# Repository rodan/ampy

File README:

an audio amplifier project that contains a mixer controlled by an MSP430 microcontroller

contents:
 hardware/power_amp  - power circuit for the amplifier
 hardware/power_pre  - power circuit used by the mixer board
 hardware/amp        - 2x25W amplifier. for a quad setup this board is used twice, for 6 channels it's used 3 times.
 hardware/mixer      - mixer board. 10 inputs, 6 outputs, 12 channels of mixing. a stereo-to-quad panning circuit is included

 firmware_mixer      - software that runs on the MSP430F5510 that is present on the mixer board
 firmware_brain      - software for the main uC (CC430F5137) that interfaces the user with the mixer board. currently user input comes via remote control presses.
 firmware_display    - software that runs on the atmega present on the BADGEr. this is a simple adaptation on Jeremy Blum's "Pi BADGEr ePaper Weather Station".

 linux               - linux client that talks over a serial link to firmware_brain and controls the mixer and the power amp

pictures now available: https://photos.app.goo.gl/L8txqSKrcZFV2BbR8

--------------------------------------------

Mixer board input

two different input methods are available, either via UART or I2C. since they use the exact same 2 pins the switch between them is a compile time option - see config.h. the i2c interface is highly recommended.

I2C implementation

the communication protocol consists of either a direct 14 byte read in which case the current settings are being shared, 2 byte writes for sending commands or 4 byte writes for sending new volume values. the slave address is 0x28.

UART commands
v___   set volume
 ||+ volume - [0-255]
 |+- channel - {r,l,b}
 +-- pga ID - [1-6]
     1: front, 2: rear, 3: line-in
     4: spdif, 5: front-rear pan, 6: center and subwoofer
m_     mute pga
 +- pga ID - [1-6]
u_     unmute pga
 +- pga ID - [1-6]
w_     write current settings to flash
 +- location [1-3]
r_     load saved settings from flash
 +- location [1-3]
s      show settings
?      show help

 homepage:        https://github.com/rodan/ampy
 author:          Petre Rodan <2b4eda@subdimension.ro>
 license:         GNU GPLv3

 parts of the code were originally forked from the openchronos-ng project [1]. 
 linux mixer control code based on alsamixer [2]

 software requirements:

   msp430 toolchain

[1] http://openchronos-ng.sourceforge.net
[2] http://www.alsa-project.org

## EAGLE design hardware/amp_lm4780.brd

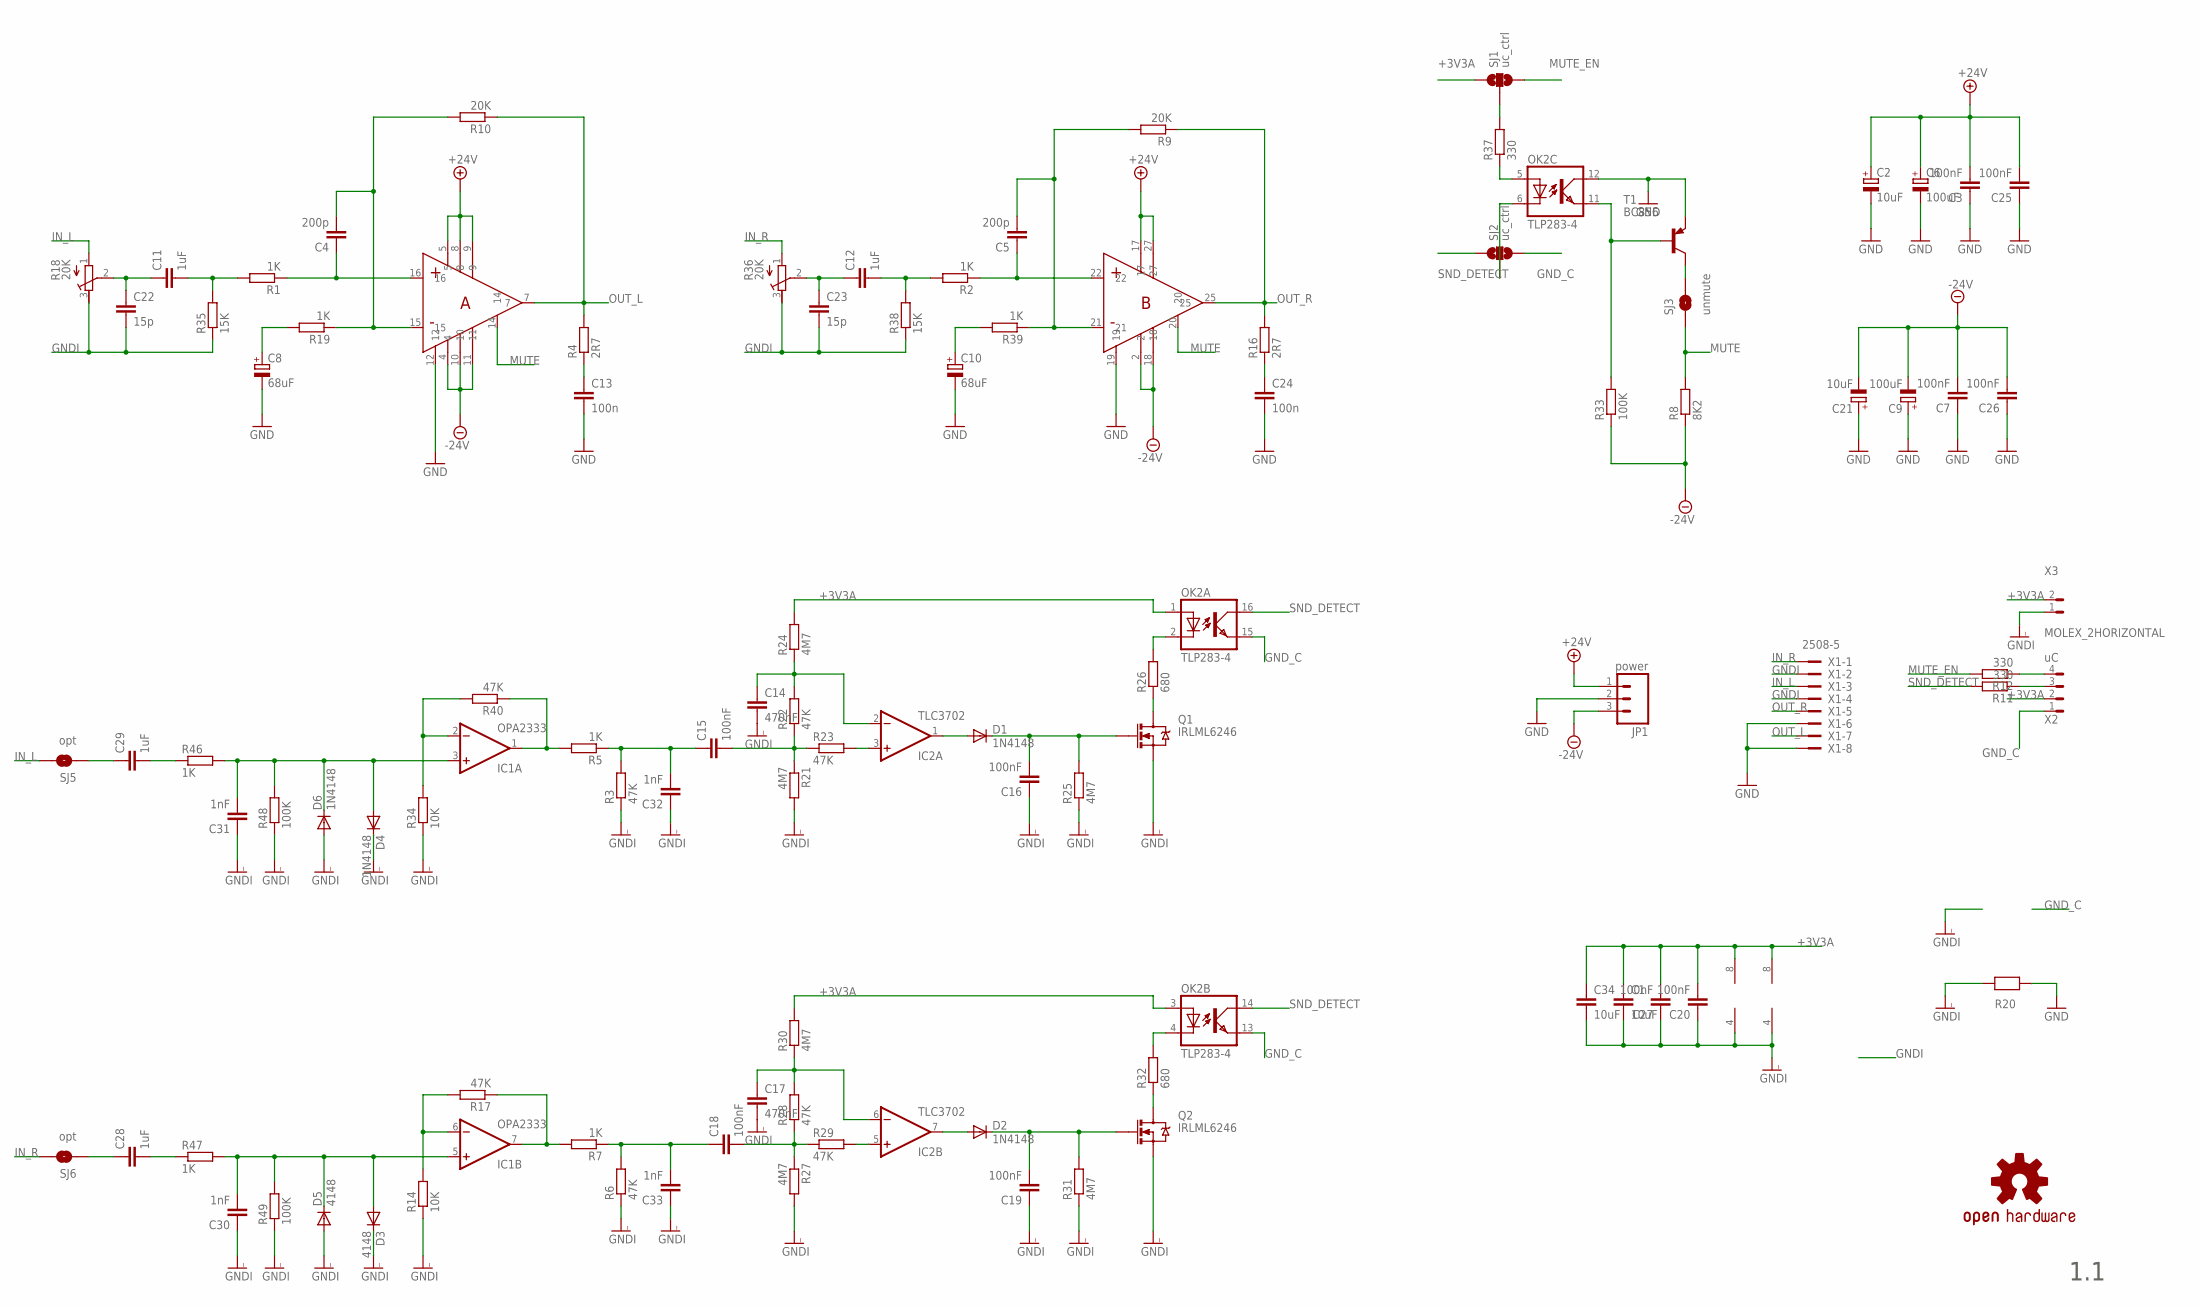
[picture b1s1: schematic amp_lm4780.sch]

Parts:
C1, C34: 10uF; C1206K
C2, C21: 10uF; PANASONIC_C
C3, C7, C15, C16, C18, C19, C20, C25, C26, C27: 100nF; C0805
C4, C5: 200p; C0805
C6, C9: 100uF; PANASONIC_G
C8, C10: 68uF; PANASONIC_E
C11, C12: 1uF; C050-035X075
C13, C24: 100n; C10B5
C14, C17: 470nF; C0805
C22, C23: 15p; C0805
C28, C29: 1uF; C0805
C30, C31, C32, C33: 1nF; C0805
D1, D2, D4, D6: 1N4148; SOD-123_MINI-SMA
D3, D5: 4148; SOD-123_MINI-SMA
IC1: OPA2333; SO08
IC2: TLC3702; SO08
JP1: power; 1X03
OK2: TLP283-4; MINI-FLAT-16
Q1, Q2: IRLML6246; SOT23-3
R1, R2, R5, R7, R46, R47: 1K; R0805W
R3, R6, R17, R22, R23, R28, R29, R40: 47K; R0805W
R4, R16: 2R7; P0613/15
R8: 8K2; R0805W
R9, R10: 20K; R0805W
R11, R12, R37: 330; R0805W
R14, R34: 10K; R0805W
R18, R36: 20K; RTRIM3339P
R19, R39: 1K; P0613/15
R20: 0R_0805; R0805W
R21, R24, R25, R27, R30, R31: 4M7; R0805W
R26, R32: 680; R0805W
R33, R48, R49: 100K; R0805W
R35, R38: 15K; R0805W
SJ1, SJ2: uc_ctrl; SJ_3_PASTE2&3
SJ3: unmute; SJ_2S-TRACE
SJ5, SJ6: opt; SJ_2S-TRACE
T1: BC856; SOT23-BEC
U$1: LM4780_H; TO220-27_HOR
U$7: OSHW-LOGOM; OSHW-LOGO-M
X1: 2508-5; PAK100/2500-5-08
X2: uC; 0530480401
X3: MOLEX_2HORIZONTAL; 0530480210

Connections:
+3V3A: C1.1, C20.2, C27.2, C34.1, IC1.8 (V+), IC2.8 (V+), OK2.1 (A), OK2.3 (A), R24.2, R30.2, SJ1.1, X2.2 (3), X3.2 (1)
+24V: C2.+, C3.2, C6.+, C25.2, JP1.1, U$1.5, U$1.8, U$1.9, U$1.17, U$1.27
-24V: C7.2, C9.-, C21.-, C26.2, JP1.3, R8.1, R33.1, U$1.2, U$1.4, U$1.10, U$1.11, U$1.18
GND: C2.-, C3.1, C6.-, C7.1, C8.-, C9.+, C10.-, C13.2, C21.+, C24.2, C25.1, C26.1, JP1.2, OK2.12 (COL), R20.2, T1.E, U$1.12, U$1.19, X1.6, X1.8
GNDI: C1.2, C14.2, C16.1, C17.2, C19.1, C20.1, C22.2, C23.2, C27.1, C30.1, C31.1, C32.1, C33.1, C34.2, D3.C, D4.C, D5.A, D6.A, IC1.4 (V-), IC2.4 (V-), Q1.2 (S), Q2.2 (S), R3.1, R6.1, R14.1, R18.3 (E), R20.1, R21.2, R25.1, R27.2, R31.1, R34.1, R35.1, R36.3 (E), R38.1, R48.1, R49.1, X1.2, X1.4, X3.1 (2)
GND_C: OK2.13 (EMIT), OK2.15 (EMIT), SJ2.3, X2.1 (4)
IN_L: R18.1 (A), SJ5.2, X1.3
IN_R: R36.1 (A), SJ6.2, X1.1
MUTE: R8.2, SJ3.1, U$1.14, U$1.20
MUTE_EN: R12.2, SJ1.3
unnamed: C5.2, R9.2, R39.1, U$1.21
unnamed: SJ3.2, T1.C
unnamed: R11.1, X2.3 (2)
unnamed: R12.1, X2.4 (1)
unnamed: IC1.6 (-IN), R14.2, R17.2
unnamed: C13.1, R4.1
unnamed: IC1.7 (OUT), R7.2, R17.1
unnamed: C4.1, R1.1, U$1.16
unnamed: C11.2, R1.2, R35.2
unnamed: C11.1, C22.1, R18.2 (S)
unnamed: C15.2, R21.1, R22.1, R23.1
unnamed: IC1.2 (-IN), R34.2, R40.2
unnamed: IC1.1 (OUT), R5.2, R40.1
unnamed: C24.1, R16.1
unnamed: D1.A, IC2.1 (OUT)
unnamed: C28.1, SJ6.1
unnamed: C30.2, D3.A, D5.C, IC1.5 (+IN), R47.2, R49.2
unnamed: C28.2, R47.1
unnamed: C29.1, SJ5.1
unnamed: IC2.3 (+IN), R23.2
unnamed: OK2.6 (C), SJ2.2
unnamed: Q1.3 (D), R26.1
unnamed: C14.1, IC2.2 (-IN), R22.2, R24.1
unnamed: C29.2, R46.1
unnamed: OK2.2 (C), R26.2
unnamed: C15.1, C32.2, R3.2, R5.1
unnamed: C31.2, D4.A, D6.C, IC1.3 (+IN), R46.2, R48.2
unnamed: C16.2, D1.C, Q1.1 (G), R25.2
unnamed: D2.A, IC2.7 (OUT)
unnamed: R37.2, SJ1.2
unnamed: C17.1, IC2.6 (-IN), R28.2, R30.1
unnamed: C18.2, R27.1, R28.1, R29.1
unnamed: C18.1, C33.2, R6.2, R7.1
unnamed: IC2.5 (+IN), R29.2
unnamed: C19.2, D2.C, Q2.1 (G), R31.2
unnamed: Q2.3 (D), R32.1
unnamed: OK2.4 (C), R32.2
unnamed: OK2.11 (EMIT), R33.2, T1.B
unnamed: C5.1, R2.1, U$1.22
unnamed: OK2.5 (A), R37.1
unnamed: C12.2, R2.2, R38.2
unnamed: C12.1, C23.1, R36.2 (S)
unnamed: C4.2, R10.2, R19.1, U$1.15
unnamed: C8.+, R19.2
unnamed: C10.+, R39.2
OUT_L: R4.2, R10.1, U$1.7, X1.7
OUT_R: R9.1, R16.2, U$1.25, X1.5
SND_DETECT: OK2.14 (COL), OK2.16 (COL), R11.2, SJ2.1

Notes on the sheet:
1.1

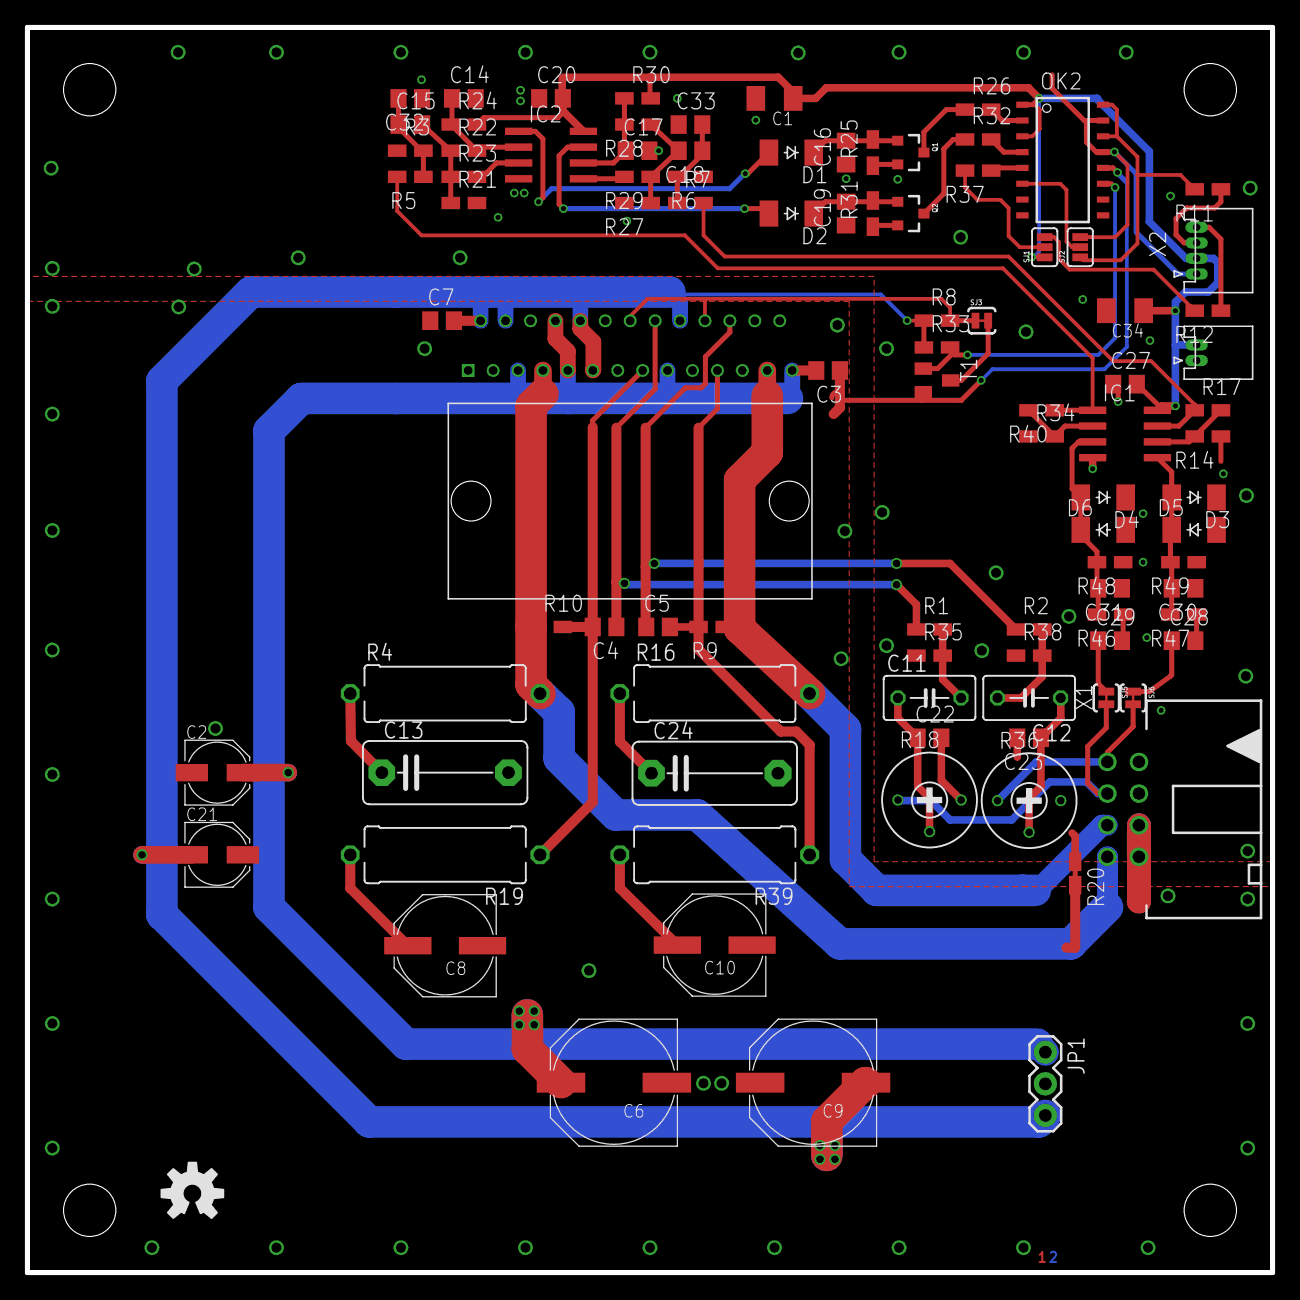
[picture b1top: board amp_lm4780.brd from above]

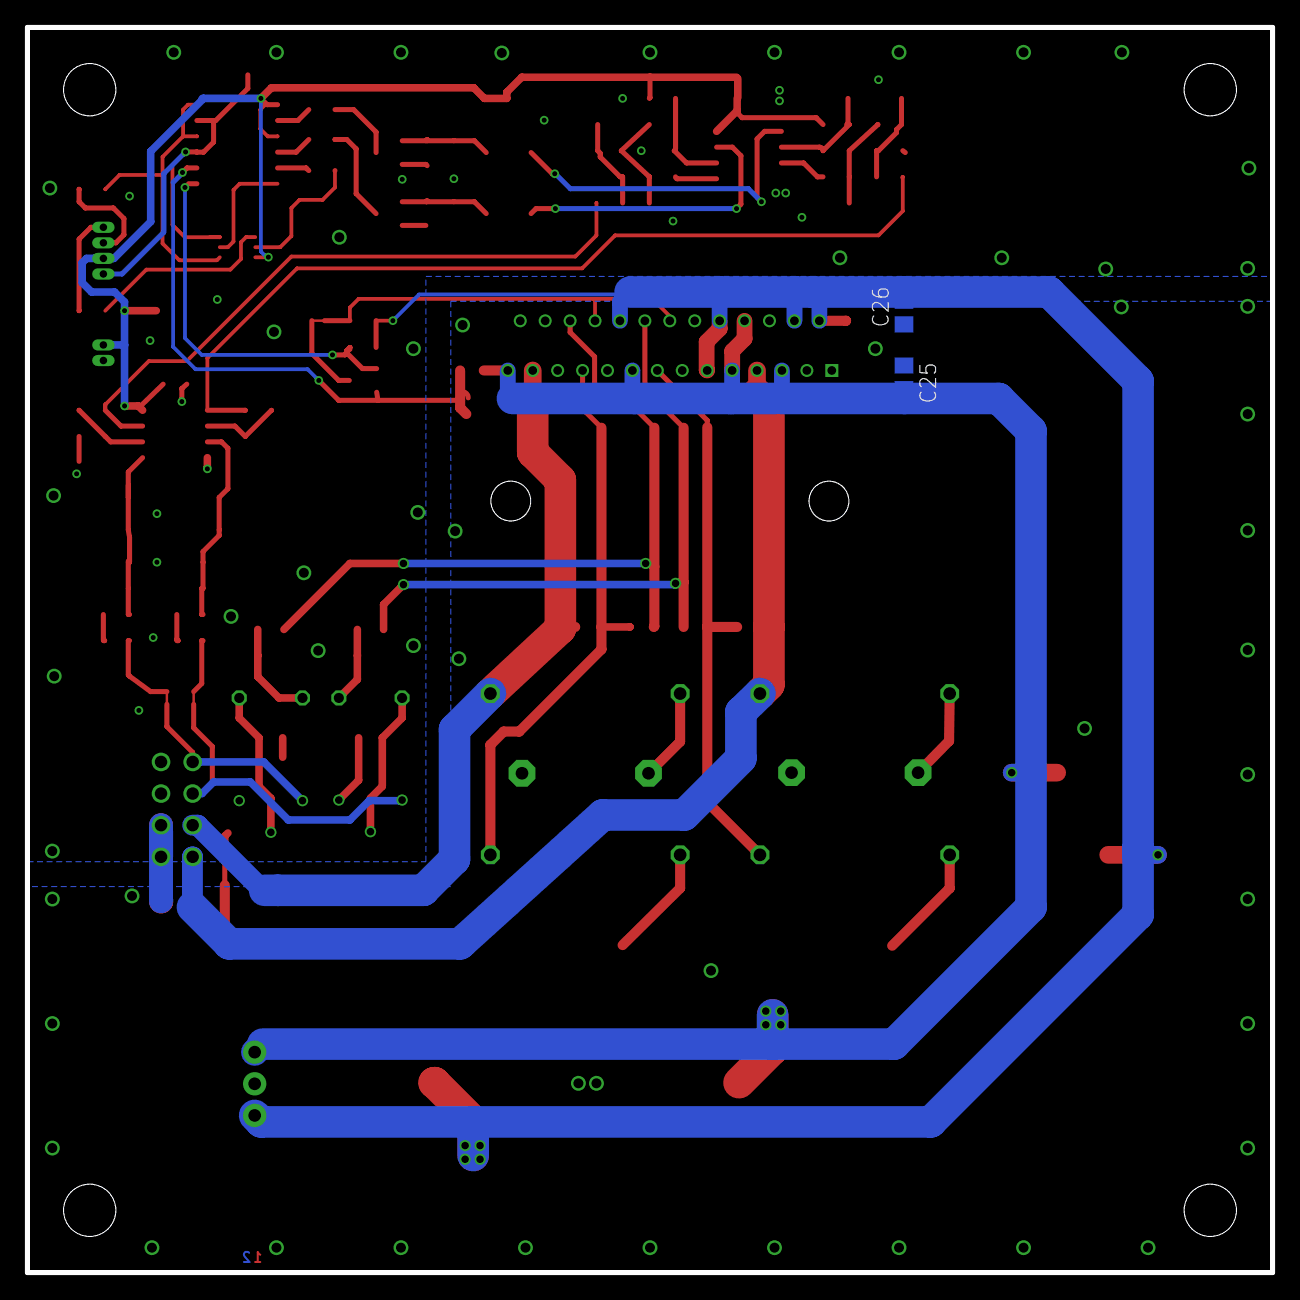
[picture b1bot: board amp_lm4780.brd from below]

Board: 4 copper layers, 100.0 x 100.0 mm, 99 parts (2 on the bottom side), 58 nets.

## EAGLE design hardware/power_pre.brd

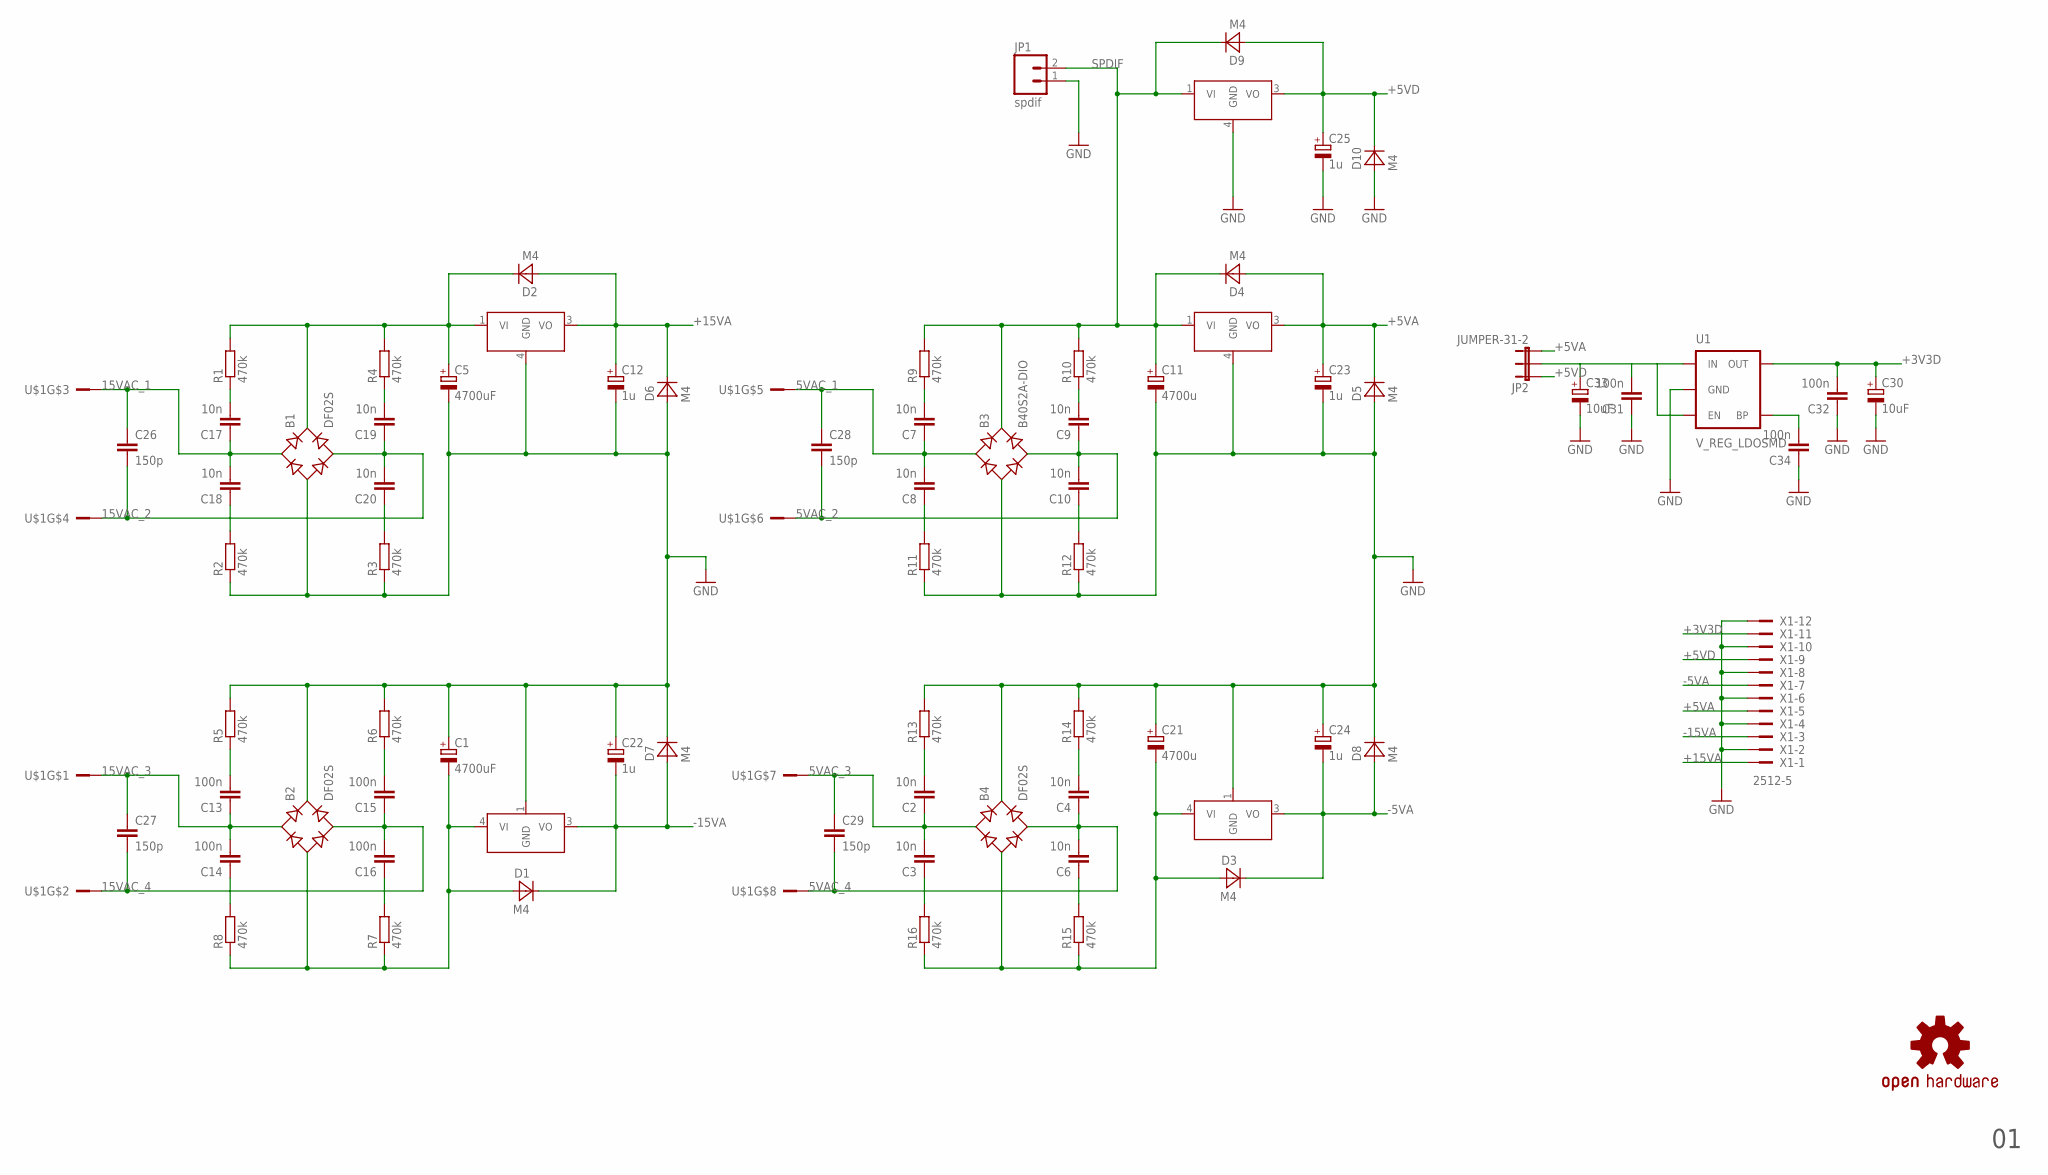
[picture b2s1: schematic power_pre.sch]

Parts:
B1, B2, B4: DF02S; DFS
B3: B40S2A-DIO; DFS
C1, C5: 4700uF; E7,5-18
C2, C3, C4, C6, C7, C8, C9, C10, C17, C18, C19, C20: 10n; C0805
C11, C21: 4700u; E7,5-16
C12, C22, C23, C24, C25: 1u; PANASONIC_B
C13, C14, C15, C16, C31, C32, C34: 100n; C0805
C26, C27, C28, C29: 150p; C5B4.5
C30, C33: 10uF; 153CLV-0405
D1, D2, D3, D4, D5, D6, D7, D8, D9, D10: M4; SMA
IC1: 7815; D2PACK
IC2: 7915; D2PACK
IC3, IC5: 7805; D2PACK
IC4: 7905; D2PACK
JP1: spdif; 1X02
JP2: JUMPER-31-2; SJ_3_PASTE1&2
R1, R2, R3, R4, R5, R6, R7, R8, R9, R10, R11, R12, R13, R14, R15, R16: 470k; R0805W
U1: V_REG_LDOSMD; SOT23-5
U$1: DEGSON_8
U$7: OSHW-LOGOM; OSHW-LOGO-M
X1: 2512-5; PAK100/2500-5-12

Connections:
5VAC_1: B3.AC1, C7.1, C8.2, C28.1, U$1.5
5VAC_2: B3.AC2, C9.1, C10.2, C28.2, U$1.6
5VAC_3: B4.AC1, C2.1, C3.2, C29.1, U$1.7
5VAC_4: B4.AC2, C4.1, C6.2, C29.2, U$1.8
15VAC_1: B1.AC1, C17.1, C18.2, C26.1, U$1.3
15VAC_2: B1.AC2, C19.1, C20.2, C26.2, U$1.4
15VAC_3: B2.AC1, C13.1, C14.2, C27.1, U$1.1
15VAC_4: B2.AC2, C15.1, C16.2, C27.2, U$1.2
+3V3D: C30.+, C32.2, U1.5 (OUT), X1.11
+5VA: C23.+, D4.A, D5.C, IC3.3 (VO), JP2.3, X1.5
+5VD: C25.+, D9.A, D10.C, IC5.3 (VO), JP2.1, X1.9
+15VA: C12.+, D2.A, D6.C, IC1.3 (VO), X1.1
-5VA: C24.-, D3.C, D8.A, IC4.3 (VO), X1.7
-15VA: C22.-, D1.C, D7.A, IC2.3 (VO), X1.3
GND: B1.-, B2.+, B3.-, B4.+, C1.+, C5.-, C11.-, C12.-, C21.+, C22.+, C23.-, C24.+, C25.-, C30.-, C31.1, C32.1, C33.-, C34.1, D5.A, D6.A, D7.C, D8.C, D10.A, IC1.4 (GND), IC2.1 (GND), IC3.4 (GND), IC4.1 (GND), IC5.4 (GND), JP1.1, R2.1, R3.1, R5.2, R6.2, R11.1, R12.1, R13.2, R14.2, U1.2 (GND), X1.2, X1.4, X1.6, X1.8, X1.10, X1.12
unnamed: C7.2, R9.1
unnamed: C18.1, R2.2
unnamed: C31.2, C33.+, JP2.2, U1.1 (IN), U1.3 (EN)
unnamed: C13.2, R5.1
unnamed: C34.2, U1.4 (BP)
unnamed: B1.+, C5.+, D2.C, IC1.1 (VI), R1.2, R4.2
unnamed: C17.2, R1.1
unnamed: B4.-, C21.-, D3.A, IC4.4 (VI), R15.1, R16.1
unnamed: C19.2, R4.1
unnamed: C20.1, R3.2
unnamed: C6.1, R15.2
unnamed: C8.1, R11.2
unnamed: B2.-, C1.-, D1.A, IC2.4 (VI), R7.1, R8.1
unnamed: C14.1, R8.2
unnamed: C16.1, R7.2
unnamed: C15.2, R6.1
unnamed: C10.1, R12.2
unnamed: C9.2, R10.1
unnamed: C3.1, R16.2
unnamed: C2.2, R13.1
unnamed: C4.2, R14.1
SPDIF: B3.+, C11.+, D4.C, D9.C, IC3.1 (VI), IC5.1 (VI), JP1.2, R9.2, R10.2

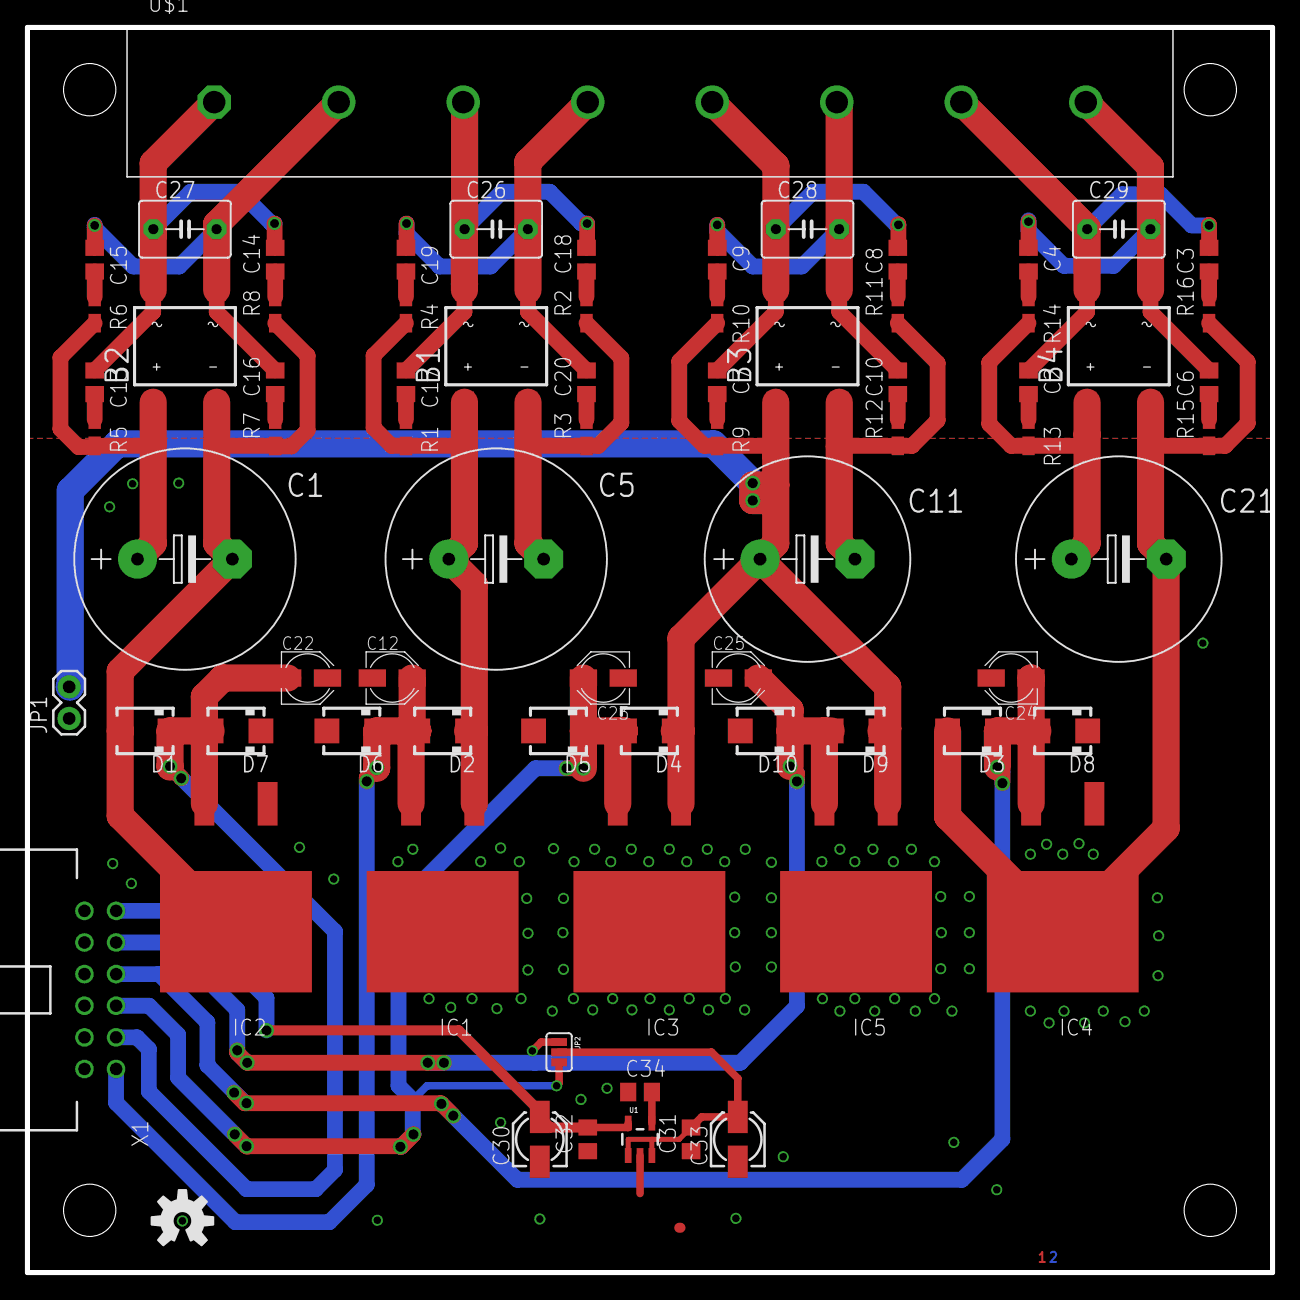
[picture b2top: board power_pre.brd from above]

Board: 4 copper layers, 100.0 x 100.0 mm, 75 parts (0 on the bottom side), 37 nets.

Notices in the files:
parts and their libraries:
SparkFun-Connectors: Licensing: Creative Commons ShareAlike 4.0 International - https://creativecommons.org/licenses/by-sa/4.0
SparkFun-Connectors: Licensing: CC v3.0 Share-Alike You are welcome to use this library for commercial purposes.
